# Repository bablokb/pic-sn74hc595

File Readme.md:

SN74HC595 based debugger for the PIC12F675
==========================================

This project provides a simple "debugger" based on the SN74HC595
shift-register. In this scenario the pic needs two GPs to clock out
data to the shift-register IC. Connecting eight leds to the IC you
can display whole bits. If you chain two 595 together, you can display
16 bit words.

To save a GP-line, we don't bother to clock out from serial-register
to parallel-register. Instead we connect SRCLK and RCLK. This needs an
additional clock-cycle for the last bit, i.e. the pic sends 9 bits
in total. With two connected 595-ICs, the pic sends 17 bits.

The example program waits for a button-press on GP5 and then displays
and increasing counter. It stops again once the counter wraps around to
zero or if the button is pressed again.

The KiCAD source of the pcb is in the directory `sn74hc595_dbg.kicad`. The
library and the example application is in the directory `src`. Note that
you need sdcc and gputils to compile and link the files, but porting
to a different toolchain should be simple.

You also need the header-files and makefile rules of my
[pic-toolchain](https://github.com/bablokb/pic-toolchain)-project.

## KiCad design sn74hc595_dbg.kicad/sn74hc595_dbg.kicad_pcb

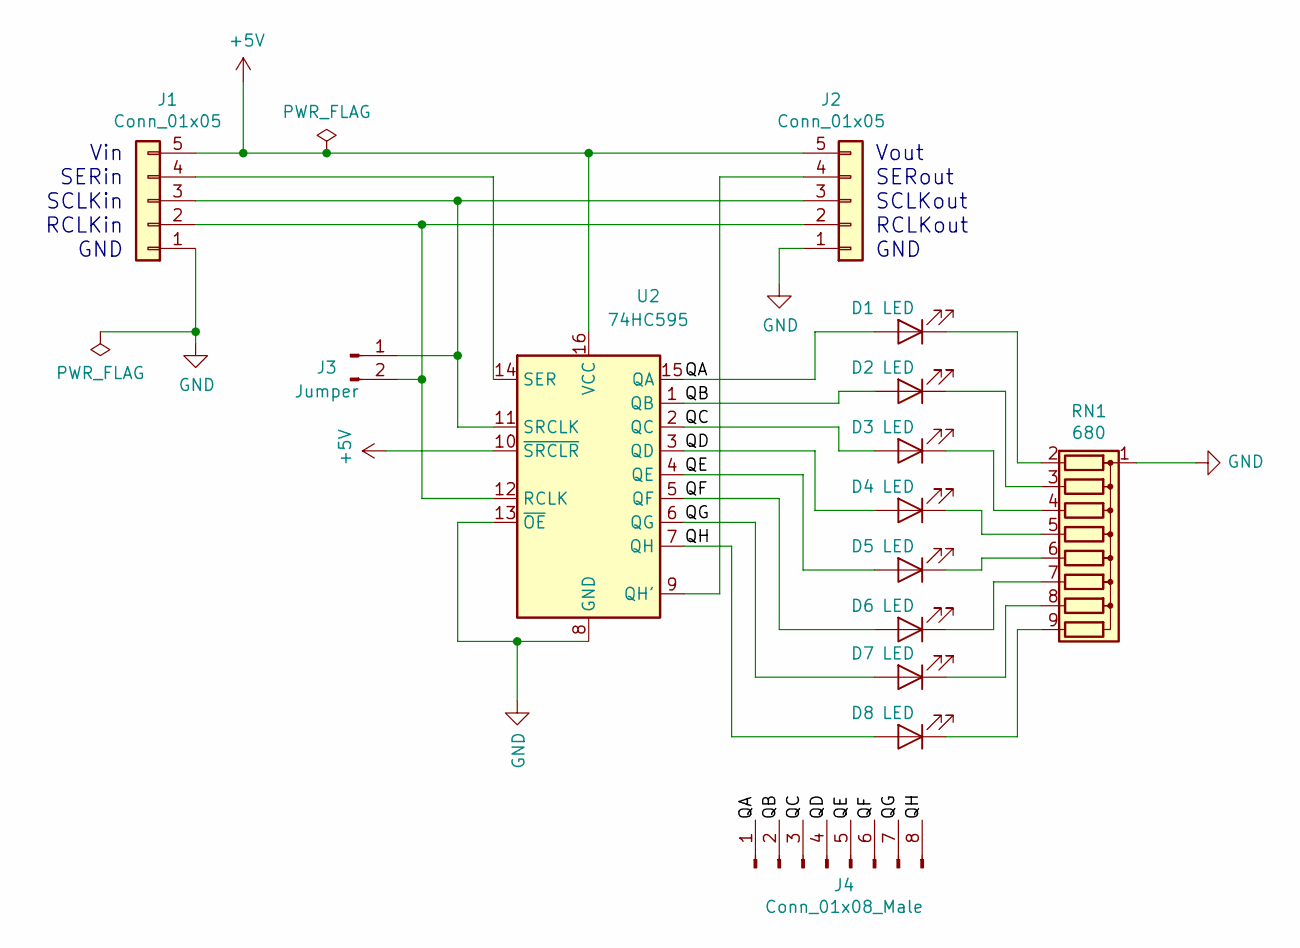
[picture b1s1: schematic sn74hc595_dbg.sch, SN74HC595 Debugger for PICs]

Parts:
D1, D2, D3, D4, D5, D6, D7, D8: LED; LED_D3.0mm
J1, J2: Conn_01x05; PinHeader_1x05_P2.54mm_Vertical
J3: Jumper; PinHeader_1x02_P2.54mm_Vertical
J4: Conn_01x08_Male; PinHeader_1x08_P2.54mm_Vertical
RN1: 680; R_Array_SIP9
U2: 74HC595; DIP-16_W7.62mm_Socket

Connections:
+5V: J1.5, J2.5, U2.10 (~SRCLR), U2.16 (VCC)
/QA: D1.2 (A), J4.1, U2.15 (QA)
/QB: D2.2 (A), J4.2, U2.1 (QB)
/QC: D3.2 (A), J4.3, U2.2 (QC)
/QD: D4.2 (A), J4.4, U2.3 (QD)
/QE: D5.2 (A), J4.5, U2.4 (QE)
/QF: D6.2 (A), J4.6, U2.5 (QF)
/QG: D7.2 (A), J4.7, U2.6 (QG)
/QH: D8.2 (A), J4.8, U2.7 (QH)
GND: J1.1, J2.1, RN1.1 (common), U2.8 (GND), U2.13 (~OE)
unnamed: D1.1 (K), RN1.2 (R1)
unnamed: D2.1 (K), RN1.3 (R2)
unnamed: D3.1 (K), RN1.4 (R3)
unnamed: D4.1 (K), RN1.5 (R4)
unnamed: D5.1 (K), RN1.6 (R5)
unnamed: D6.1 (K), RN1.7 (R6)
unnamed: D7.1 (K), RN1.8 (R7)
unnamed: D8.1 (K), RN1.9 (R8)
unnamed: J1.2, J2.2, J3.2, U2.12 (RCLK)
unnamed: J1.3, J2.3, J3.1, U2.11 (SRCLK)
unnamed: J1.4, U2.14 (SER)
unnamed: J2.4, U2.9 (QH')

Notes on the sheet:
Vin SERin SCLKin RCLKin GND
Vout SERout SCLKout RCLKout GND

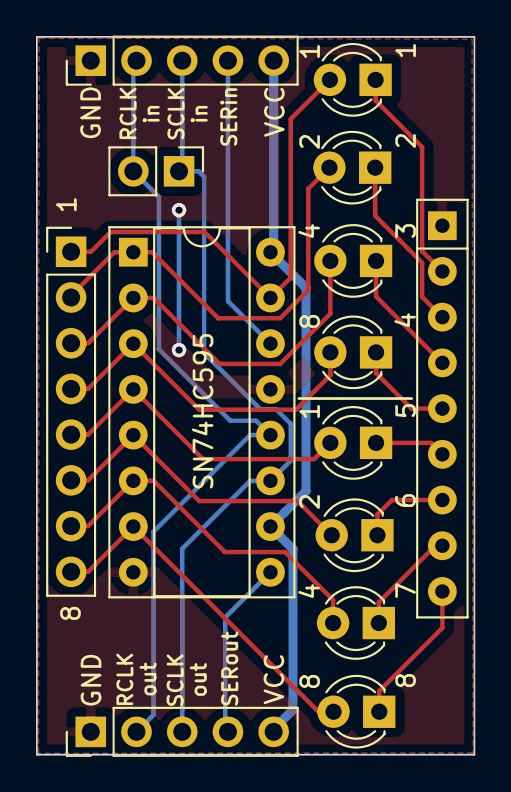
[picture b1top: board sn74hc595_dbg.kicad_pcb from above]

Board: 2 copper layers, 24.3 x 39.9 mm, 14 parts (0 on the bottom side), 22 nets.

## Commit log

2020-04-19 Rev 1: initial commit
2020-04-20 swapped horizontal LEDs with vertical LEDs
2020-04-20 optimized layout, added labels
2020-04-29 create src and populate
2020-04-29 changed path to rules.inc
2020-04-30 minor wording-change
2020-04-30 Rev 2: connector for output-pins / jumper for SCLK/RCLK connection
2020-05-01 optimized labels
2020-05-10 fixed link to github-repository
2020-05-10 updated project description in file headers
2020-05-19 link to pcb.jpg
2020-05-21 bugfix: wrong order of bits during shift-out
2020-05-25 support so_addr() in example
2020-09-06 more generic code (support chips with RA-pins)
2020-09-29 renamed pin-names
2020-09-29 define default pin-numbers
2020-09-30 use sdcc for linking
2020-09-30 support PIC12F683 and PIC12F1840
2020-10-12 removed include (not necessary)
2020-10-14 add PIN_BTN and LENGTH to make-variables
2020-10-14 make GP for button configurable / fix small bugs
2020-11-20 reorganized files
2020-11-20 updated to new standard
2020-11-20 refactor code (use picconfig.h)
2020-11-20 swapped default pin-allocation
2020-11-21 minor fixes / support IOC for PIC12F1612
2020-12-26 removed files part of (global) pic-toolchain
2020-12-26 use global pic-toolchain rules and includes
2021-01-14 migrate to pic-as (xc8-assember)
2021-01-14 migrated to standard
2021-02-07 add semicolon after CONFIG_WORDS
2021-03-13 use IOC-macros
2021-03-21 migrated to new register-names
